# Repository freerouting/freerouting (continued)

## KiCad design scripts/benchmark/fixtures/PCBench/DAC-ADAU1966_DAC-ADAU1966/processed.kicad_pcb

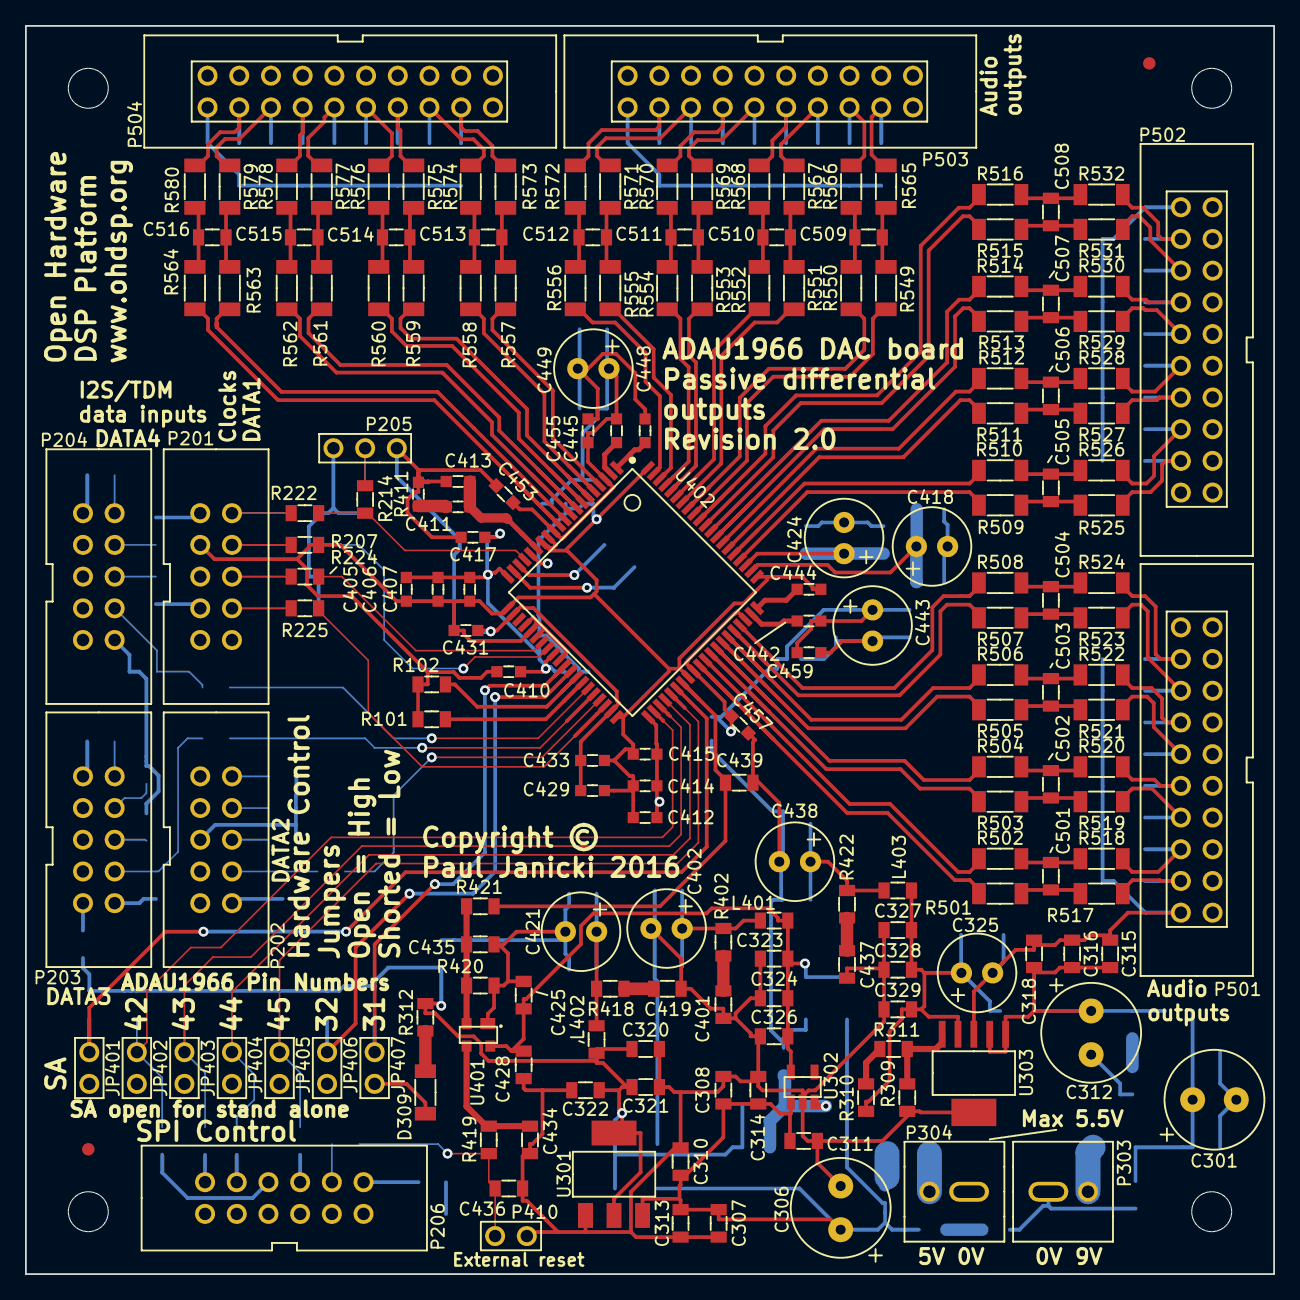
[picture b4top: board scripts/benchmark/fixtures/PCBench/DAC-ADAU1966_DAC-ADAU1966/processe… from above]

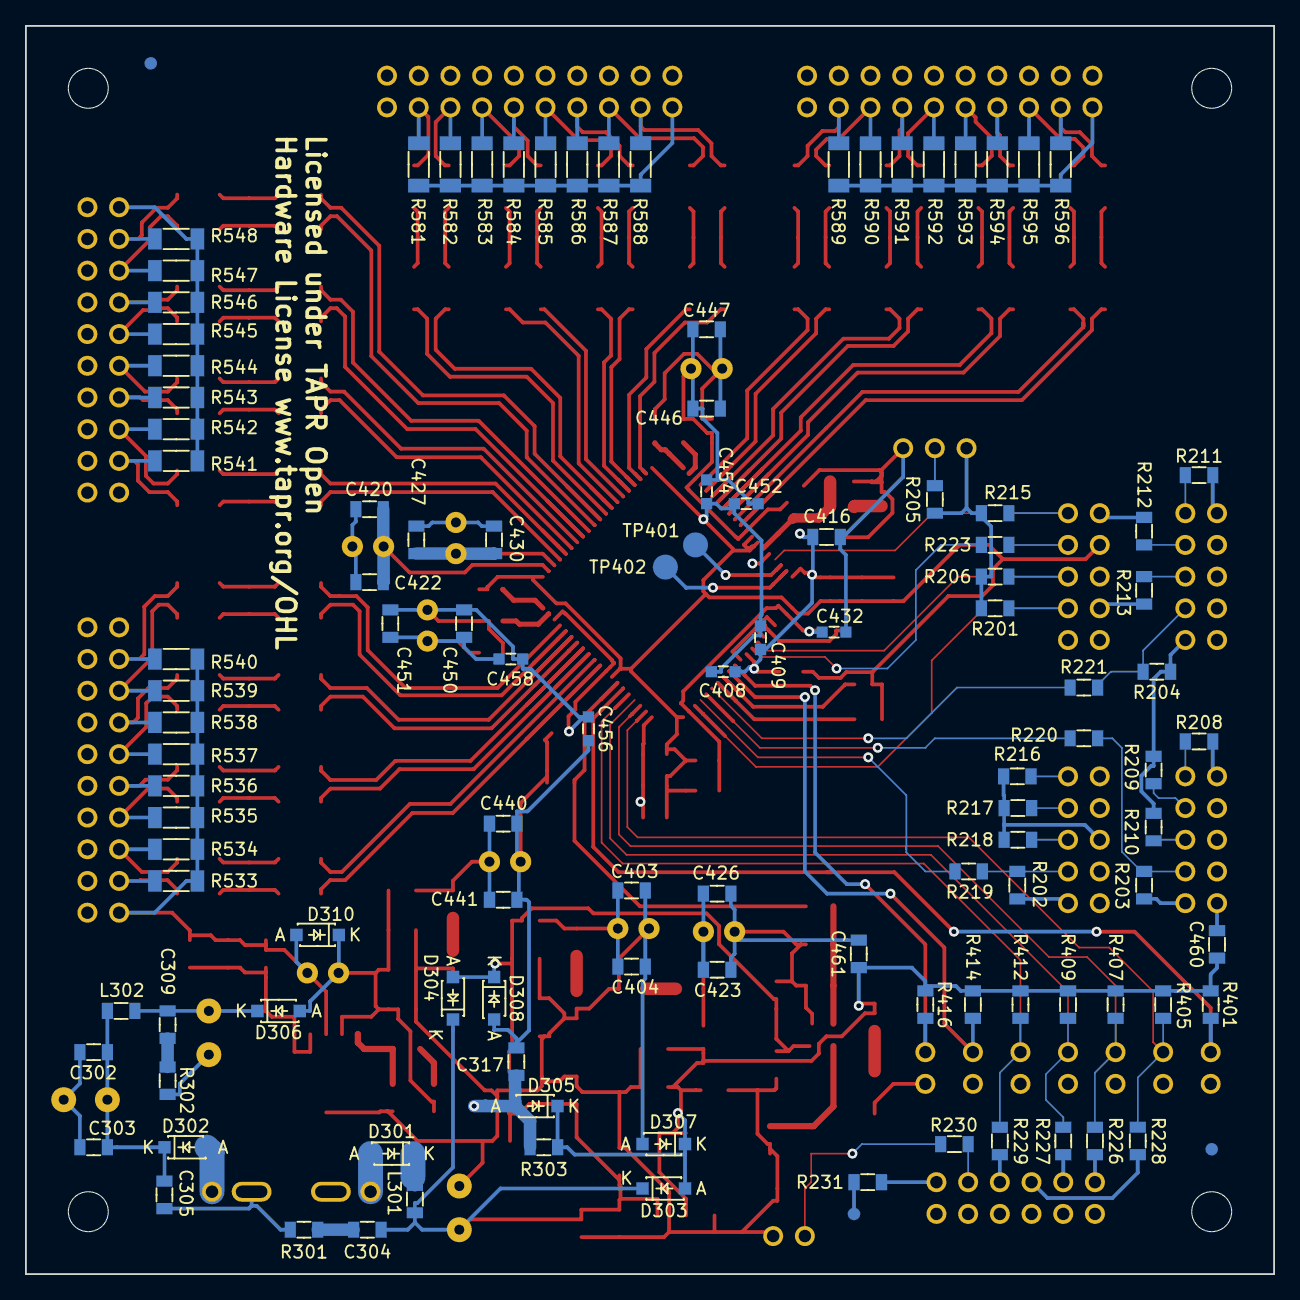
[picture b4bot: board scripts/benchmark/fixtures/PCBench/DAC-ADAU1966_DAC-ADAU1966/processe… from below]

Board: 4 copper layers, 100.0 x 100.0 mm, 306 parts (114 on the bottom side), 172 nets.

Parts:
C301, C306, C312: 220u; CAP-TH-D8mmP3.5mm
C302, C307, C308, C315, C317, C320, C323, C327, C403, C416, C420, C423, C427, C440: 22u; SMD-0805
C303, C310, C311, C316, C321, C324, C328, C404, C422, C426, C428, C430, C434, C436, C439, C441, C446, C450, C460: 100n; SMD-0805
C304, C309, C401, C419, C437: 100p; SMD-0805
C305, C313, C314, C318, C322, C326, C329, C447, C451: 10n; SMD-0805
C325, C402, C418, C421, C424, C438: 220u; CAP-TH-D6.3mmP2.5mm
C405, C408, C412, C429, C432, C452, C454, C456, C458: 1u; SMD-0603
C406, C409, C414, C417, C431, C433, C453, C455, C457, C459: 100n; SMD-0603
C407, C410, C415: 10n; SMD-0603
C411: 5n6; SMD-0603
C413: 390p; SMD-0603
C425, C461: 10u; SMD-0805
C435: N/F; SMD-0805
C442, C444, C445, C448: 470n; SMD-0603
C443, C449: 47u; CAP-TH-D6.3mmP2.5mm
C501, C502, C503, C504, C505, C506, C507, C508, C509, C510, C511, C512, C513, C514, C515, C516: 2n7; SMD-0805
D301, D302, D303, D304, D306, D307, D308, D310: SS14L; DIODE-SOD-123
D305: B130LAW-7-F; DIODE-SOD-123
D309: Green LED 1206; SMD-1206
FID1, FID2, FID3, FID4: MNT_HOLE; FID-1MM-3MM
JP401, JP402, JP403, JP404, JP405, JP406, JP407: CONN_2x1; CONN_SIL_2_1MM
L301, L302, L401, L402, L403: 600R@100MHz; SMD-0805
MNT301, MNT302, MNT303, MNT304: MNT_HOLE; MNT_HOLE_3.2mm
P201, P202, P203, P204: CONN_02X05; CONN_DIL_2X5_BOX_1MM
P205: CONN_3x1; CONN_SIL_3_1MM
P206: CONN_02X06; CONN_DIL_2X6_BOX_1MM
P303, P304: CONN_2x1; CONN-2WAY-2.54mm-3.81mm-SPACING
P410: CONN_2x1; CONN_SIL_2_1MM
P501, P502, P503, P504: CONN_02X10; CONN_DIL_2X10_BOX_1MM
R101, R102, R419: 1k; SMD-0805
R201, R202, R203, R204, R205, R206, R207, R214, R215: N/F; SMD-0805
R208, R209, R210, R211, R212, R213, R216, R217, R218, R401, R405, R407, R409, R412, R414, R416: 10k; SMD-0805
R219, R220, R221, R222, R223, R224, R225, R227, R228, R229, R230, R231, R310: 0; SMD-0805
R226: 75; SMD-0805
R301, R302, R402, R418, R422: 47; SMD-0805
R303: 47k; SMD-0805
R309: 2k2; SMD-0805
R311: 6k8; SMD-0805
R312: 470; SMD-0805
R411: 562; SMD-0603
R420: 100k; SMD-0805
R421: 100; SMD-0805
R501, R502, R503, R504, R505, R506, R507, R508, R509, R510, R511, R512, R513, R514, R515, R516, R549, R550, R551, R552, R553, R554, R555, R556, R557, R558, R559, R560, R561, R562, R563, R564: 240; SMD-1206
R517, R518, R519, R520, R521, R522, R523, R524, R525, R526, R527, R528, R529, R530, R531, R532, R565, R566, R567, R568, R569, R570, R571, R572, R573, R574, R575, R576, R577, R578, R579, R580: 100; SMD-1206
R533, R534, R535, R536, R537, R538, R539, R540, R541, R542, R543, R544, R545, R546, R547, R548, R581, R582, R583, R584, R585, R586, R587, R588, R589, R590, R591, R592, R593, R594, R595, R596: 100k; SMD-1206
TP101: Test point; TP-1mm
TP401, TP402: Test point; TP-2mm
U301: TLV1117LV33DCY; IC-SOT-223
U302: TLV70025DDC; IC-SOT23-5
U303: TPS7A4501; IC-SOT223-6
U401: ADM811ZART; IC-SOT143
U402: IC-DAC-ADAU1966; IC-LQFP80-P065

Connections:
/ADAU1966/AVDD: C438.1, C440.1, C441.1, C442.1, C443.1, C445.1, C446.1, C447.1, C449.1, C450.1, C451.1, C452.1, C453.1, C454.1, C455.1, C456.1, C457.1, C458.1, C459.1, L403.2, R422.1, U402.3, U402.12, U402.49, U402.58
/ADAU1966/DACOUT_LRCLK: R223.2, U402.28
/ADAU1966/DACOUT_SDATA1: R225.2, U402.38
/ADAU1966/DACOUT_SDATA2: R219.2, U402.37
/ADAU1966/DACOUT_SDATA3: R220.2, U402.36
/ADAU1966/DACOUT_SDATA4: R221.2, U402.35
/ADAU1966/DACOUT_SDATA5: R101.1, U402.34
/ADAU1966/DACOUT_SDATA6: R102.1, U402.33
/ADAU1966/DAC_CLK: JP404.1, R227.1, R409.1, U402.44
/ADAU1966/DAC_CS: JP405.1, R229.1, R412.1, U402.45
/ADAU1966/DAC_MISO: JP403.1, R226.1, R407.1, U402.43
/ADAU1966/DAC_MOSI: JP402.1, R228.1, R405.1, U402.42
/ADAU1966/DAC_RESET: C439.1, R421.1, U402.47
/ADAU1966/DSDATA7: JP406.1, R414.1, U402.32
/ADAU1966/DSDATA8: JP407.1, R416.1, U402.31
/ADAU1966/DVDD: C402.1, C403.1, C404.1, C405.1, C406.1, C407.1, C408.1, C409.1, C410.1, C412.1, C414.1, C415.1, C416.1, C417.1, L401.2, R402.1, U402.16, U402.20, U402.29, U402.41
/ADAU1966/IOVDD: C421.1, C423.1, C426.1, C429.1, C431.1, C432.1, C433.1, L402.2, R418.1, U402.22, U402.39
/ADAU1966/LF: C411.1, C413.1, U402.15
/ADAU1966/MAN_RST_IN: C436.1, P410.1, R230.1, R419.2
/ADAU1966/MCLK: R214.2, R222.2, U402.17
/ADAU1966/OUT_1P: R501.1, U402.50
/ADAU1966/OUT_2P: R503.1, U402.52
/ADAU1966/OUT_3P: R505.1, U402.54
/ADAU1966/OUT_4P: R507.1, U402.56
/ADAU1966/OUT_5P: R509.1, U402.64
/ADAU1966/OUT_6P: R511.1, U402.66
/ADAU1966/OUT_7P: R513.1, U402.68
/ADAU1966/OUT_8P: R515.1, U402.70
/ADAU1966/OUT_9P: R549.1, U402.72
/ADAU1966/OUT_10P: R551.1, U402.74
/ADAU1966/OUT_11P: R553.1, U402.76
/ADAU1966/OUT_12P: R555.1, U402.78
/ADAU1966/OUT_13P: R557.1, U402.4
/ADAU1966/OUT_14P: R559.1, U402.6
/ADAU1966/OUT_15P: R561.1, U402.8
/ADAU1966/OUT_16P: R563.1, U402.10
/ADAU1966/SA: JP401.1, R401.1, U402.46
/AnaloguePassiveFilters/N1: R502.1, U402.51
/AnaloguePassiveFilters/N2: R504.1, U402.53
/AnaloguePassiveFilters/N3: R506.1, U402.55
/AnaloguePassiveFilters/N4: R508.1, U402.57
/AnaloguePassiveFilters/N5: R510.1, U402.65
/AnaloguePassiveFilters/N6: R512.1, U402.67
/AnaloguePassiveFilters/N7: R514.1, U402.69
/AnaloguePassiveFilters/N8: R516.1, U402.71
/AnaloguePassiveFilters/N9: R550.1, U402.73
/AnaloguePassiveFilters/N10: R552.1, U402.75
/AnaloguePassiveFilters/N11: R554.1, U402.77
/AnaloguePassiveFilters/N12: R556.1, U402.79
/AnaloguePassiveFilters/N13: R558.1, U402.5
/AnaloguePassiveFilters/N14: R560.1, U402.7
/AnaloguePassiveFilters/N15: R562.1, U402.9
/AnaloguePassiveFilters/N16: R564.1, U402.11
/Connectors/BCLK: R224.2, U402.27
/Connectors/GPIO: R231.1, TP101.1
GNDA: C301.2, C302.2, C303.2, C305.2, C306.2, C307.2, C308.2, C310.2, C311.2, C312.2, C313.2, C314.2, C315.2, C316.2, C317.2, C318.2, C320.2, C321.2, C322.2, C323.2, C324.2, C325.2, C326.2, C327.2, C328.2, C329.2, C401.2, C402.2, C403.2, C404.2, C405.2, C406.2, C407.2, C408.2, C409.2, C410.2, C412.2, C413.2, C414.2, C415.2, C416.2, C417.2, C418.2, C419.2, C420.2, C421.2, C422.2, C423.2, C424.2, C425.2, C426.2, C427.2, C428.2, C429.2, C430.2, C431.2, C432.2, C433.2, C434.2, C435.2, C436.2, C437.2, C438.2, C439.2, C440.2, C441.2, C443.2, C444.2, C446.2, C447.2, C448.2, C449.2, C450.2, C451.2, C452.2, C453.2, C454.2, C455.2, C456.2, C457.2, C458.2, C459.2, C460.2, C461.2, D307.1, D308.1, D309.2, D310.1, JP401.2, JP402.2, JP403.2, JP404.2, JP405.2, JP406.2, JP407.2, P201.1, P201.3, P201.5, P201.7, P201.9, P201.10, P202.1, P202.3, P202.5, P202.7, P202.9, P202.10, P203.1, P203.3, P203.5, P203.7, P203.9, P203.10, P204.1, P204.3, P204.5, P204.7, P204.9, P204.10, P205.1, P205.3, P206.1, P206.3, P206.5, P206.7, P206.9, P206.11, P303.2, P304.2, P410.2, P501.1, P501.2, P501.3, P501.5, P501.7, P501.9, P501.11, P501.13, P501.15, P501.17, P501.19, P501.20, P502.1, P502.2, P502.3, P502.5, P502.7, P502.9, P502.11, P502.13, P502.15, P502.17, P502.19, P502.20, P503.1, P503.2, P503.3, P503.5, P503.7, P503.9, P503.11, P503.13, P503.15, P503.17, P503.19, P503.20, P504.1, P504.2, P504.3, P504.5, P504.7, P504.9, P504.11, P504.13, P504.15, P504.17, P504.19, P504.20, R101.2, R102.2, R201.1, R202.1, R203.1, R204.1, R205.1, R206.1, R207.1, R208.2, R209.2, R210.2, R211.2, R212.2, R213.2, R215.1, R216.2, R217.2, R218.2, R301.2, R302.2, R309.2, R411.2, R420.1, R533.2, R534.2, R535.2, R536.2, R537.2, R538.2, R539.2, R540.2, R541.2, R542.2, R543.2, R544.2, R545.2, R546.2, R547.2, R548.2, R581.2, R582.2, R583.2, R584.2, R585.2, R586.2, R587.2, R588.2, R589.2, R590.2, R591.2, R592.2, R593.2, R594.2, R595.2, R596.2, U301.1, U302.2, U303.3, U401.1, U402.13, U402.14, U402.21, U402.24, U402.25, U402.26, U402.30, U402.40, U402.48, U402.61, U402.80
unnamed: C301.1, C302.1, C303.1, C305.1, D302.2, L302.1
unnamed: C304.1, C306.1, C307.1, C308.1, C310.1, C311.1, C313.1, C314.1, D303.2, D304.2, L301.2, U301.3, U302.1
unnamed: C304.2, R301.1
unnamed: C309.1, C312.1, C315.1, C316.1, C318.1, D306.2, L302.2, U303.1, U303.2
unnamed: C309.2, R302.1
unnamed: C317.1, D305.1, R303.2, U302.3
unnamed: C401.1, R402.2
unnamed: C411.2, R411.1
unnamed: C418.1, C420.1, C422.1, U402.62
unnamed: C419.1, R418.2
unnamed: C424.1, C427.1, C430.1, U402.63
unnamed: C434.1, R419.1, U401.3
unnamed: C435.1, R420.2, R421.2, U401.2
unnamed: C437.1, R422.2
unnamed: C442.2, U402.59
unnamed: C444.1, U402.60
unnamed: C445.2, U402.2
unnamed: C448.1, U402.1
unnamed: C501.1, R502.2, R518.1
unnamed: C501.2, R501.2, R517.1
unnamed: C502.1, R504.2, R520.1
unnamed: C502.2, R503.2, R519.1
unnamed: C503.1, R506.2, R522.1
unnamed: C503.2, R505.2, R521.1
unnamed: C504.1, R508.2, R524.1
unnamed: C504.2, R507.2, R523.1
unnamed: C505.1, R510.2, R526.1
unnamed: C505.2, R509.2, R525.1
unnamed: C506.1, R512.2, R528.1
unnamed: C506.2, R511.2, R527.1
unnamed: C507.1, R514.2, R530.1
unnamed: C507.2, R513.2, R529.1
unnamed: C508.1, R516.2, R532.1
unnamed: C508.2, R515.2, R531.1
unnamed: C509.1, R550.2, R566.1
unnamed: C509.2, R549.2, R565.1
unnamed: C510.1, R552.2, R568.1
unnamed: C510.2, R551.2, R567.1
unnamed: C511.1, R554.2, R570.1
unnamed: C511.2, R553.2, R569.1
unnamed: C512.1, R556.2, R572.1
unnamed: C512.2, R555.2, R571.1
unnamed: C513.1, R558.2, R574.1
unnamed: C513.2, R557.2, R573.1
unnamed: C514.1, R560.2, R576.1
unnamed: C514.2, R559.2, R575.1
unnamed: C515.1, R562.2, R578.1
unnamed: C515.2, R561.2, R577.1
unnamed: C516.1, R564.2, R580.1
unnamed: C516.2, R563.2, R579.1
unnamed: D301.1, P304.1
unnamed: D301.2, L301.1
unnamed: D302.1, P303.1
unnamed: D309.1, R312.2
unnamed: P201.2, R215.2, R222.1
unnamed: P201.4, R207.2, R223.1
unnamed: P201.6, R206.2, R224.1
unnamed: P201.8, R201.2, R225.1
unnamed: P202.2, R216.1
unnamed: P202.4, R217.1
unnamed: P202.6, R218.1
unnamed: P202.8, R202.2, R219.1
unnamed: P203.2, R208.1
unnamed: P203.4, R209.1
unnamed: P203.6, R210.1
unnamed: P203.8, R203.2, R220.1
unnamed: P204.2, R211.1
unnamed: P204.4, R212.1
unnamed: P204.6, R213.1
unnamed: P204.8, R204.2, R221.1
unnamed: P205.2, R205.2, R214.1
unnamed: P206.2, R226.2
unnamed: P206.4, R227.2
unnamed: P206.6, R228.2
unnamed: P206.8, R229.2
unnamed: P206.10, R230.2
unnamed: P206.12, R231.2
unnamed: P501.4, R517.2, R533.1
unnamed: P501.6, R518.2, R534.1
unnamed: P501.8, R519.2, R535.1
unnamed: P501.10, R520.2, R536.1
unnamed: P501.12, R521.2, R537.1
unnamed: P501.14, R522.2, R538.1
unnamed: P501.16, R523.2, R539.1
unnamed: P501.18, R524.2, R540.1
unnamed: P502.4, R525.2, R541.1
unnamed: P502.6, R526.2, R542.1
unnamed: P502.8, R527.2, R543.1
unnamed: P502.10, R528.2, R544.1
unnamed: P502.12, R529.2, R545.1
unnamed: P502.14, R530.2, R546.1
unnamed: P502.16, R531.2, R547.1
unnamed: P502.18, R532.2, R548.1
unnamed: P503.4, R565.2, R581.1
unnamed: P503.6, R566.2, R582.1
unnamed: P503.8, R567.2, R583.1
unnamed: P503.10, R568.2, R584.1
unnamed: P503.12, R569.2, R585.1
unnamed: P503.14, R570.2, R586.1
unnamed: P503.16, R571.2, R587.1
unnamed: P503.18, R572.2, R588.1
unnamed: P504.4, R573.2, R589.1
unnamed: P504.6, R574.2, R590.1
unnamed: P504.8, R575.2, R591.1
unnamed: P504.10, R576.2, R592.1
unnamed: P504.12, R577.2, R593.1
unnamed: P504.14, R578.2, R594.1
unnamed: P504.16, R579.2, R595.1
unnamed: P504.18, R580.2, R596.1
unnamed: R309.1, R311.2, U303.5
unnamed: R310.1, R311.1
unnamed: TP401.1, U402.18
unnamed: TP402.1, U402.19
VAA: C325.1, C327.1, C328.1, C329.1, D306.1, D310.2, L403.1, R310.2, U303.4
VDD: C323.1, C324.1, C326.1, C425.1, C428.1, D304.1, D308.2, L401.1, U302.5, U401.4
VPP: C320.1, C321.1, C322.1, C460.1, C461.1, D303.1, D305.2, D307.2, L402.1, R303.1, R312.1, R401.2, R405.2, R407.2, R409.2, R412.2, R414.2, R416.2, U301.2

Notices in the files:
scripts/benchmark/fixtures/PCBench/DAC-ADAU1966_DAC-ADAU1966/processed.kicad_pcb:
Licensed under the TAPR Open Hardware License (www.tapr.org/OHL). This documentation
Copyright Paul Janicki 2016
Copyright ©
Licensed under TAPR Open
